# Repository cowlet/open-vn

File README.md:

# Open VN: An Industrial Wireless Sensor Network R&D platform

## Background

Electrical utilities and industrial manufacturers are continuously striving for new ways to lower costs and extend equipment lifetime through effective asset management strategies. One established method for determining the condition of plant is online condition monitoring (CM), which aims to detect and manage incipient defects at the earliest possible stage.

To reduce costs and simplify the deployment of CM systems, industry is turning to the state-of-the-art in industrial wireless sensor network (IWSN) technology to build secure and robust monitoring networks designed for hostile industrial environments. As part of a research project funded by National Grid, an open and extensible IWSN platform has been developed to support research into novel ways of monitoring electrical plant health. A wireless CM network based upon this platform is deployed into the University of Strathclyde Microgrid Laboratory and plans are in place for the platform to be rolled out and extended into the Power Network Demonstration Centre.

The platform, while being initially used for smart grid monitoring applications, is application-independent and can be used as the basis of any industrial wireless sensing project. With the hardware schematics released under a Creative Commons licence and the software components released under the MIT licence, this enables universities and industry to leverage the platform royalty free in their research and development.

## Technology

The platform incorporates an integrated hardware and software platform for researching and developing industrial wireless sensing applications based upon the International Society of Automation (ISA) wireless standard ISA100.11a. The platform contains designs for all interfacing hardware and software required to use ISA100.11a radio hardware from [Nivis LLC](http://www.nivis.com), providing a fast track to developing custom standards-based wireless sensors while cutting the cost of developing such systems.

The hardware and software are primarily designed to be used with the open-source Arduino platform which has become a preferred platform for collaborative and university research projects. The platform was designed for extensibility, so both hardware and software components can be easily extended for use with other embedded microprocessor architectures.

## Key Benefits

* An off-the-shelf, standards-based, industrial wireless sensor network research and development platform.
* Licensed under MIT and Creative Commons licences, allowing the platform components to be used in commercial projects.
* Modular and flexible, designed to be used with any microcontroller/microprocessor architecture dependent on the application.

## Contributors

* Pete Baker &lt;peteb4ker@gmail.com&gt;
* Victoria Catterson &lt;vic@cowlet.org&gt;

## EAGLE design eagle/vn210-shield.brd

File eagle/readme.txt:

= LICENCE = 

These designs are under the Creative Commons Attribution Sharealike licence 3.0

- http://creativecommons.org/licenses/by-sa/2.0/

= OVERVIEW = 

* nivis-vn210.lbr: Eagle library components for the VN210
* vn210-breakout.*: Schematic and layout for the VN210 breakout.  THis is the small board that you solder the VN210 radio to.
* vn210-shield.*: Schematic and layout for the VN210 shield.  This connects the VN210 breakout to an arduino.

= INSTALLING =

1) Download and install eagle cadsoft.
2) Check out this folder into your eagle project folder.   
3) This requires components from the SparkFun eagle library.  Download it from:

-  https://github.com/sparkfun/SparkFun-Eagle-Library

= MAKING A NEW SHIELD DESIGN =

The shield connects the VN210 breakout to an Ardunio.  It is possible to implement new layout for the
same schematic to connect the breakout board to other microcontrollers should you need to.  The same
schematic can be used (for 5V microcontrollers anyway).  3V microcontrollers dont need the interfacing diodes.

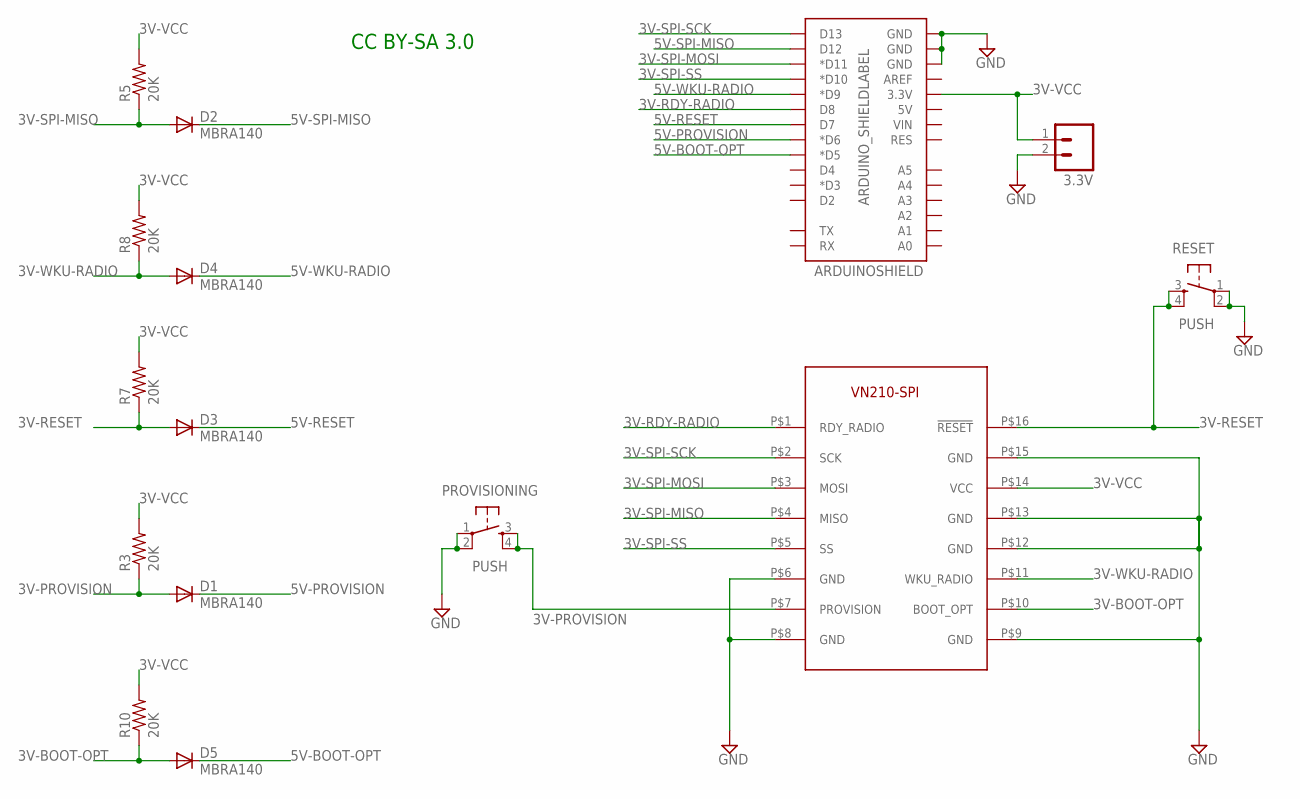
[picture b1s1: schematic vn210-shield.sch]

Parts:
3.3V: M02LOCK; 1X02_LOCK
ARDUINOSHIELD: ARDUINO_SHIELDLABEL; DUEMILANOVE_SHIELD
D1, D2, D3, D4, D5: MBRA140; SMA-DIODE_ALT
PROVISIONING: PUSH; TACTILE-PTH
R3, R5, R7, R8, R10: 20K; 1206
RESET: PUSH; TACTILE-PTH
U$1: VN210-BREAKOUT

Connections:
3V-BOOT-OPT: D5.A, R10.1, U$1.P$10 (BOOT_OPT)
3V-PROVISION: D1.A, PROVISIONING.3, PROVISIONING.4, R3.1, U$1.P$7 (PROVISION)
3V-RDY-RADIO: ARDUINOSHIELD.D8, U$1.P$1 (RDY_RADIO)
3V-RESET: D3.A, R7.1, RESET.3, RESET.4, U$1.P$16 (!RESET)
3V-SPI-MISO: D2.A, R5.1, U$1.P$4 (MISO)
3V-SPI-MOSI: ARDUINOSHIELD.D11 (*D11), U$1.P$3 (MOSI)
3V-SPI-SCK: ARDUINOSHIELD.D13, U$1.P$2 (SCK)
3V-SPI-SS: ARDUINOSHIELD.D10 (*D10), U$1.P$5 (SS)
3V-VCC: 3.3V.1, ARDUINOSHIELD.3.3V, R3.2, R5.2, R7.2, R8.2, R10.2, U$1.P$14 (VCC)
3V-WKU-RADIO: D4.A, R8.1, U$1.P$11 (WKU_RADIO)
5V-BOOT-OPT: ARDUINOSHIELD.D5 (*D5), D5.C
5V-PROVISION: ARDUINOSHIELD.D6 (*D6), D1.C
5V-RESET: ARDUINOSHIELD.D7, D3.C
5V-SPI-MISO: ARDUINOSHIELD.D12, D2.C
5V-WKU-RADIO: ARDUINOSHIELD.D9 (*D9), D4.C
GND: 3.3V.2, ARDUINOSHIELD.GND@0 (GND), ARDUINOSHIELD.GND@1 (GND), ARDUINOSHIELD.GND@2 (GND), PROVISIONING.1, PROVISIONING.2, RESET.1, RESET.2, U$1.P$6 (GND), U$1.P$8 (GND), U$1.P$9 (GND), U$1.P$12 (GND), U$1.P$13 (GND), U$1.P$15 (GND)

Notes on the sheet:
CC BY-SA 3.0

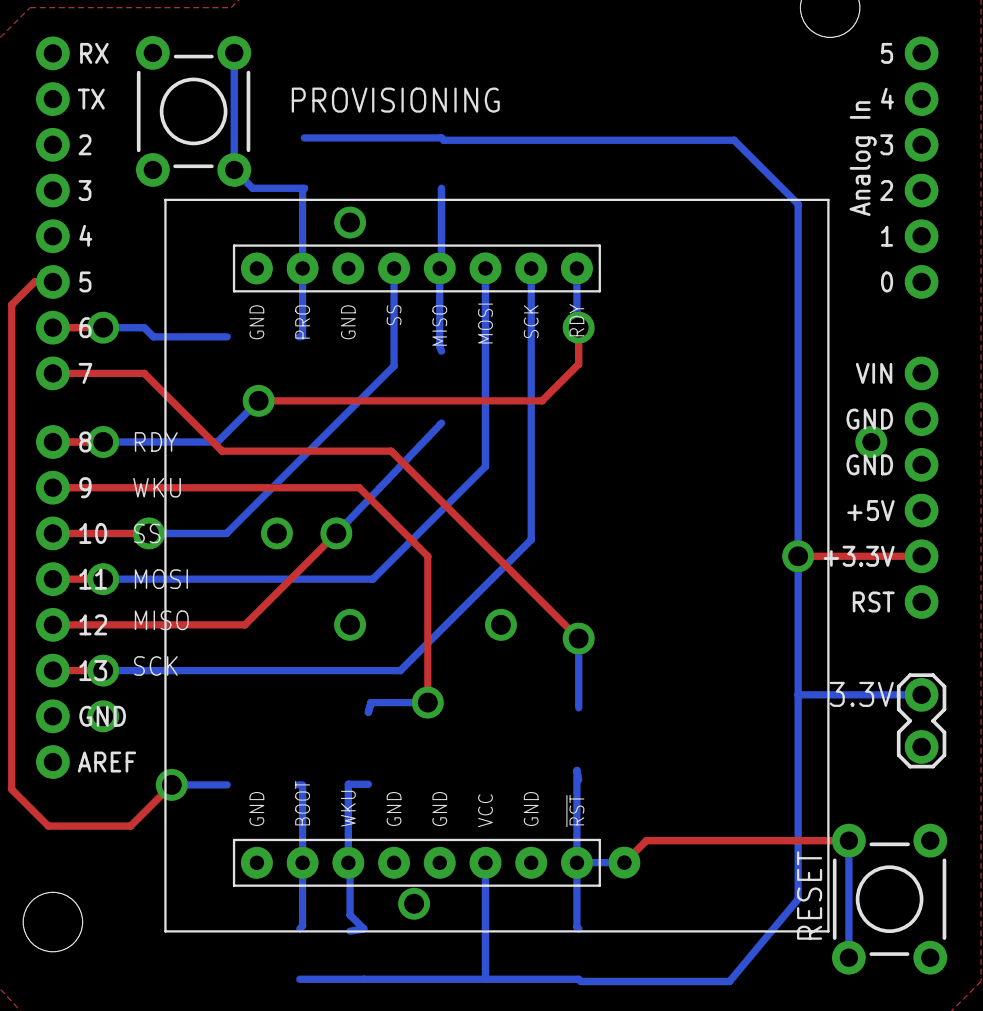
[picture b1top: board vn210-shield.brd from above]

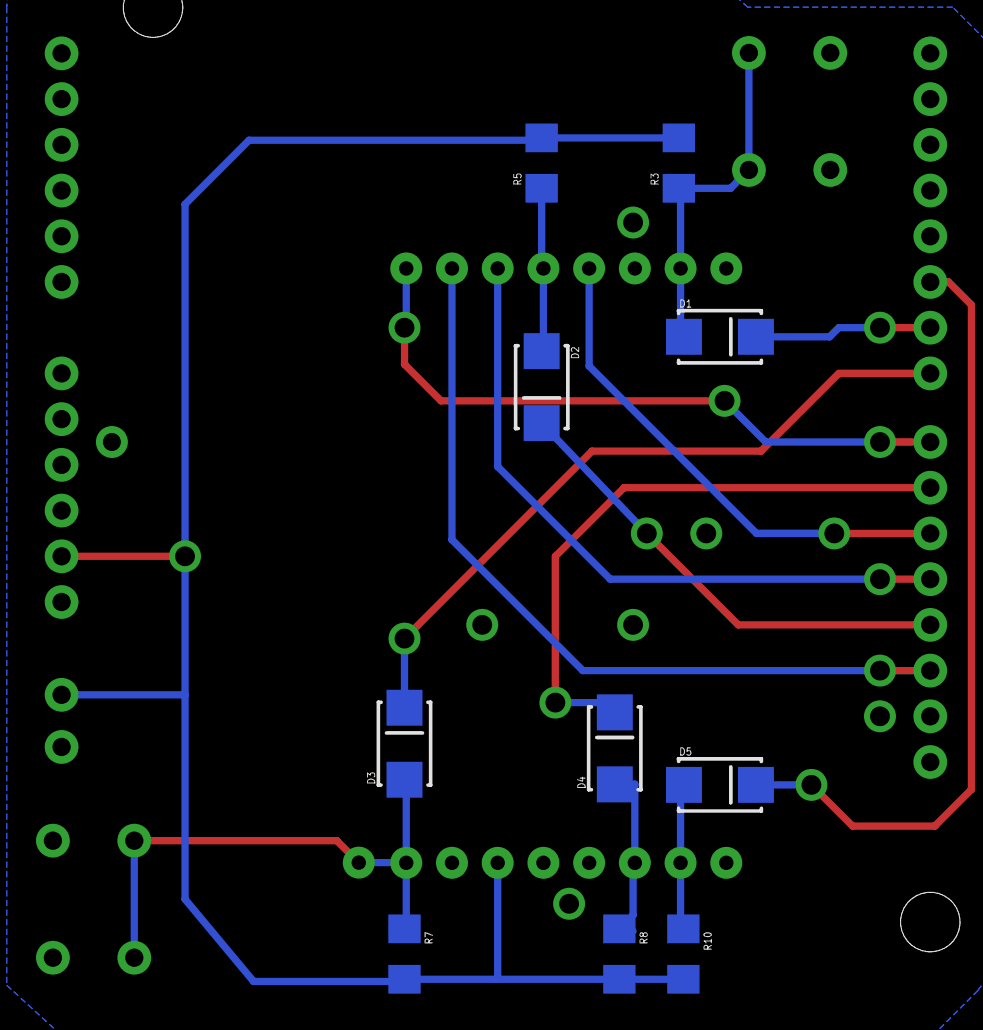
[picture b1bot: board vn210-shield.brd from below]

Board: 2 copper layers, 15 parts (10 on the bottom side), 16 nets.

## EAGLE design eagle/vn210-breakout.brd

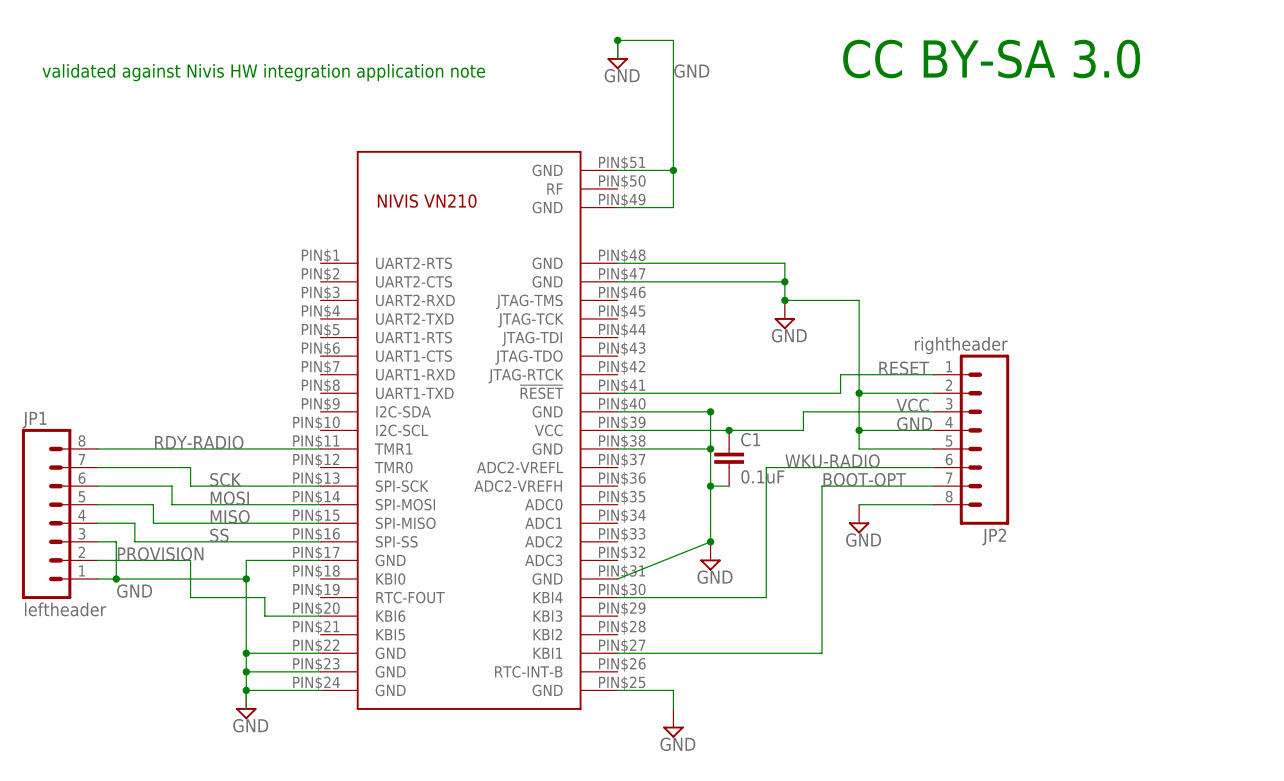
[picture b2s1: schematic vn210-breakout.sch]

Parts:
C1: 0.1uF; C1206
JP1: leftheader; 1X08
JP2: rightheader; 1X08
U$1: VN210

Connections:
BOOT-OPT: JP2.7, U$1.PIN$27 (KBI1)
GND: C1.2, JP1.1, JP1.3, JP2.2, JP2.4, JP2.5, JP2.8, U$1.PIN$17 (GND), U$1.PIN$22 (GND), U$1.PIN$23 (GND), U$1.PIN$24 (GND), U$1.PIN$25 (GND), U$1.PIN$31 (GND), U$1.PIN$38 (GND), U$1.PIN$40 (GND), U$1.PIN$47 (GND), U$1.PIN$48 (GND), U$1.PIN$49 (GND), U$1.PIN$51 (GND)
MISO: JP1.5, U$1.PIN$15 (SPI-MISO)
MOSI: JP1.6, U$1.PIN$14 (SPI-MOSI)
PROVISION: JP1.2, U$1.PIN$20 (KBI6)
RDY-RADIO: JP1.8, U$1.PIN$11 (TMR1)
RESET: JP2.1, U$1.PIN$41 (!RESET)
SCK: JP1.7, U$1.PIN$13 (SPI-SCK)
SS: JP1.4, U$1.PIN$16 (SPI-SS)
VCC: C1.1, JP2.3, U$1.PIN$39 (VCC)
WKU-RADIO: JP2.6, U$1.PIN$30 (KBI4)

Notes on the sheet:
validated against Nivis HW integration application note
CC BY-SA 3.0

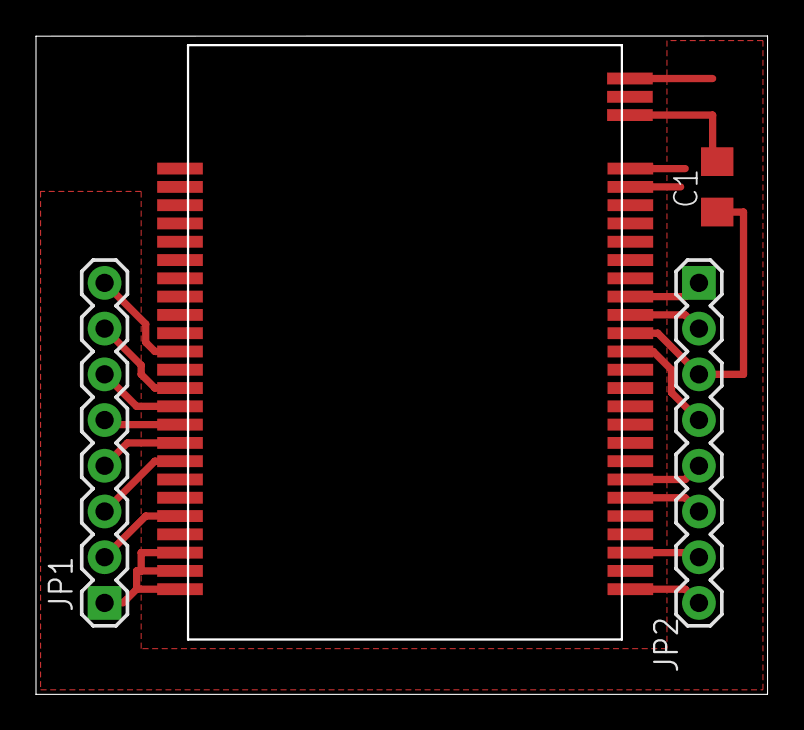
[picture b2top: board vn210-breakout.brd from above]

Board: 2 copper layers, 40.5 x 36.4 mm, 4 parts (0 on the bottom side), 11 nets.

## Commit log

2012-12-23 Initial project commit
2012-12-23 Remove unneeded file
2012-12-23 Add licensing information
2013-08-06 Fix bug where SCADA registers are never updated
2013-08-29 Add SCADARegister library source and header
    This library is required by the VN210_MAX6675 example.
2013-08-29 Amend MAX6675 example
    After updating the UAP registers with new values, reset the data
    store. This means each update reports on the previous time window
    and not the full monitoring period.
2014-06-09 Update readme and licence information
2014-06-09 Update license

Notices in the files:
parts and their libraries:
SparkFun: Licensing: CC v3.0 Share-Alike You are welcome to use this library for commercial purposes.
